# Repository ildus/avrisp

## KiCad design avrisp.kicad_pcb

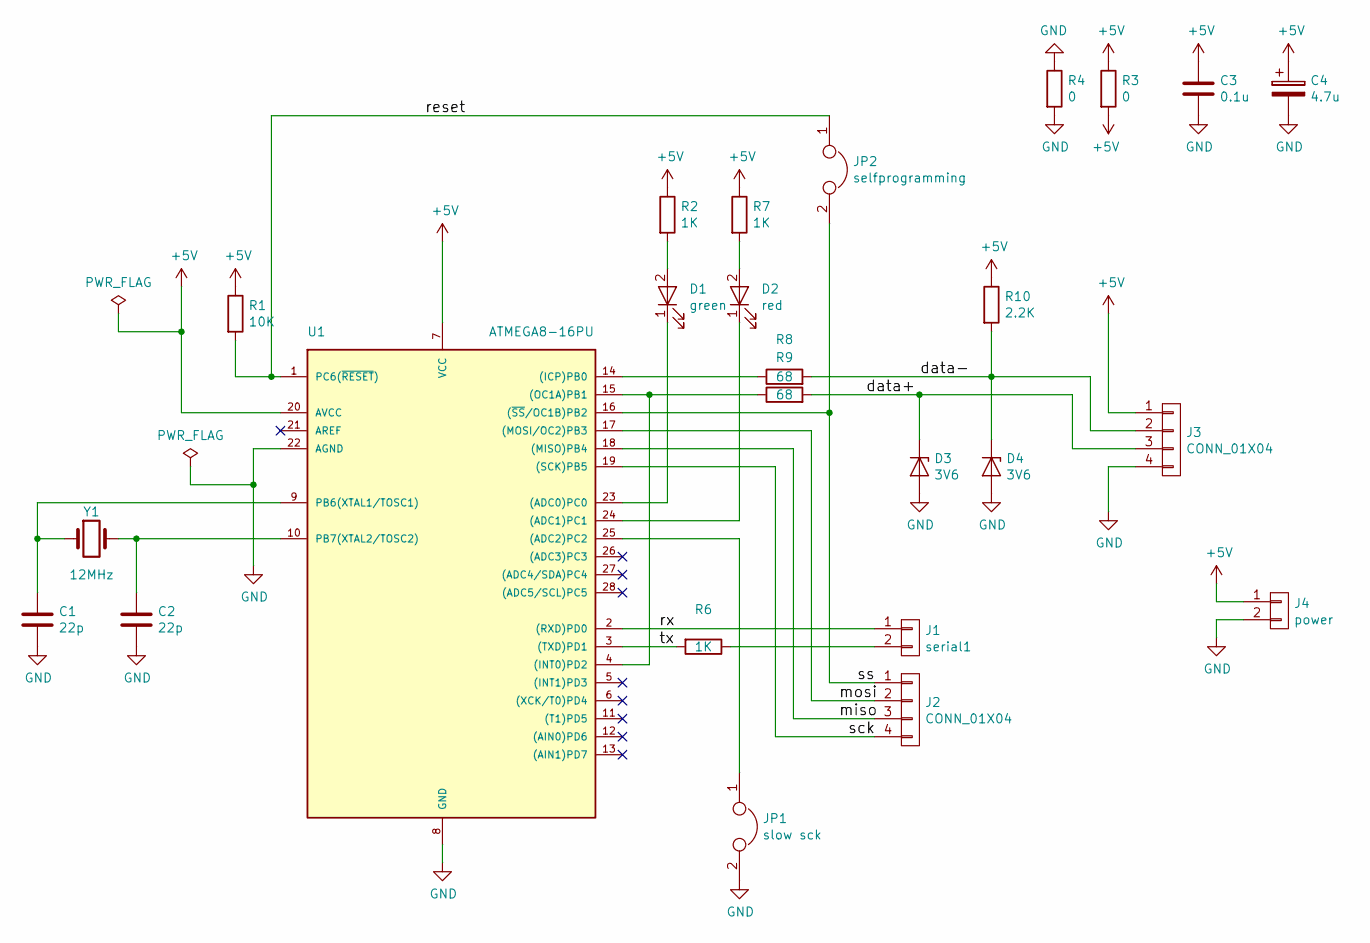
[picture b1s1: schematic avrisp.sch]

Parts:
C1, C2: 22p; C_0805_HandSoldering
C3: 0.1u; C_0805_HandSoldering
C4: 4.7u; CP_Radial_D4.0mm_P2.00mm
D1: green; LED_1206
D2: red; LED_1206
D3, D4: 3V6; SOT-23
J1: serial1; Molex_KK-6410-02_02x2.54mm_Straight
J2, J3: CONN_01X04; Molex_KK-6410-04_04x2.54mm_Straight
J4: power; Molex_KK-6410-02_02x2.54mm_Straight
JP1: slow sck; Molex_KK-6410-02_02x2.54mm_Straight
JP2: selfprogramming; Molex_KK-6410-02_02x2.54mm_Straight
R1: 10K; R_1206
R2, R6, R7: 1K; R_1206
R3, R4: 0; R_1206
R8, R9: 68; R_1206
R10: 2.2K; R_1206
U1: ATMEGA8-16PU; DIP-28_W7.62mm
Y1: 12MHz; Crystal_HC50_Vertical

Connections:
+5V: C3.1, C4.1, J3.1, J4.1, R1.1, R2.1, R3.1, R3.2, R7.1, R10.1, U1.7 (VCC), U1.20 (AVCC)
/data+: D3.3 (K), J3.3, R9.2
/data-: D4.3 (K), J3.2, R8.2, R10.2
/miso: J2.3, U1.18 ((MISO)PB4)
/mosi: J2.2, U1.17 ((MOSI/OC2)PB3)
/reset: JP2.1, R1.2, U1.1 (PC6(~RESET~))
/rx: J1.1, U1.2 ((RXD)PD0)
/sck: J2.4, U1.19 ((SCK)PB5)
/ss: J2.1, JP2.2, U1.16 ((~SS~/OC1B)PB2)
/tx: R6.2, U1.3 ((TXD)PD1)
GND: C1.2, C2.2, C3.2, C4.2, D3.1 (A), D4.1 (A), J3.4, J4.2, JP1.2, R4.1, R4.2, U1.8 (GND), U1.22 (AGND)
unnamed: C1.1, U1.9 (PB6(XTAL1/TOSC1)), Y1.1
unnamed: C2.1, U1.10 (PB7(XTAL2/TOSC2)), Y1.2
unnamed: D1.1 (K), U1.23 ((ADC0)PC0)
unnamed: D1.2 (A), R2.2
unnamed: D2.1 (K), U1.24 ((ADC1)PC1)
unnamed: D2.2 (A), R7.2
unnamed: J1.2, R6.1
unnamed: JP1.1, U1.25 ((ADC2)PC2)
unnamed: R8.1, U1.14 ((ICP)PB0)
unnamed: R9.1, U1.4 ((INT0)PD2), U1.15 ((OC1A)PB1)

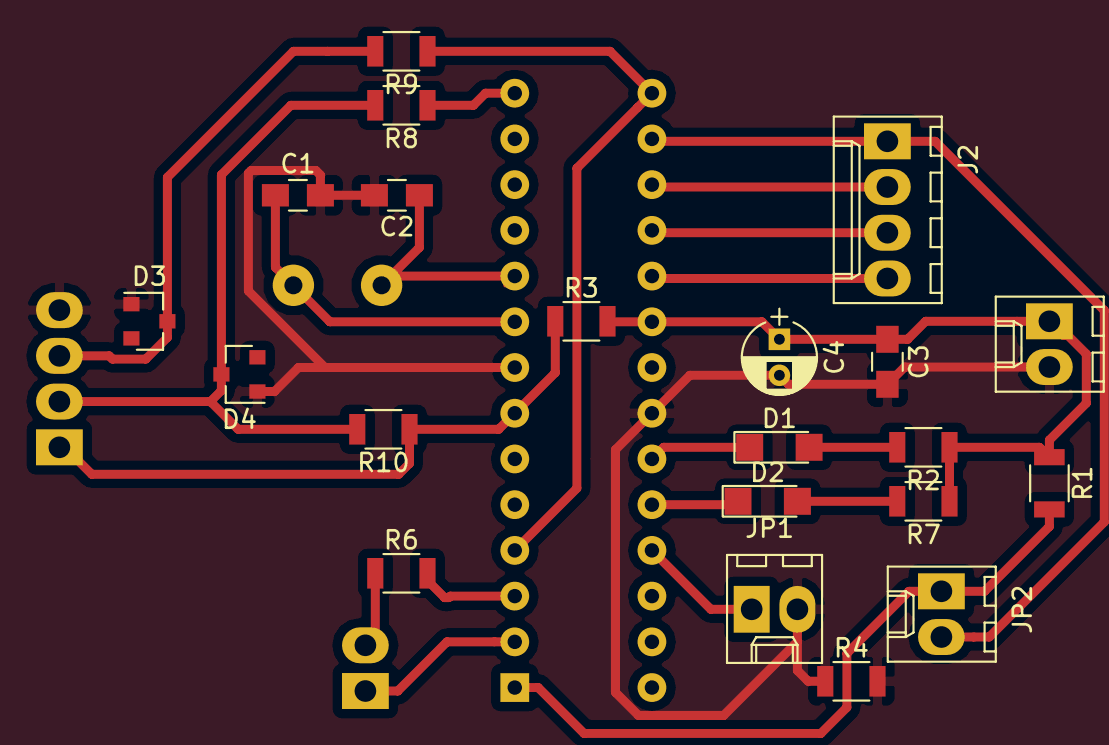
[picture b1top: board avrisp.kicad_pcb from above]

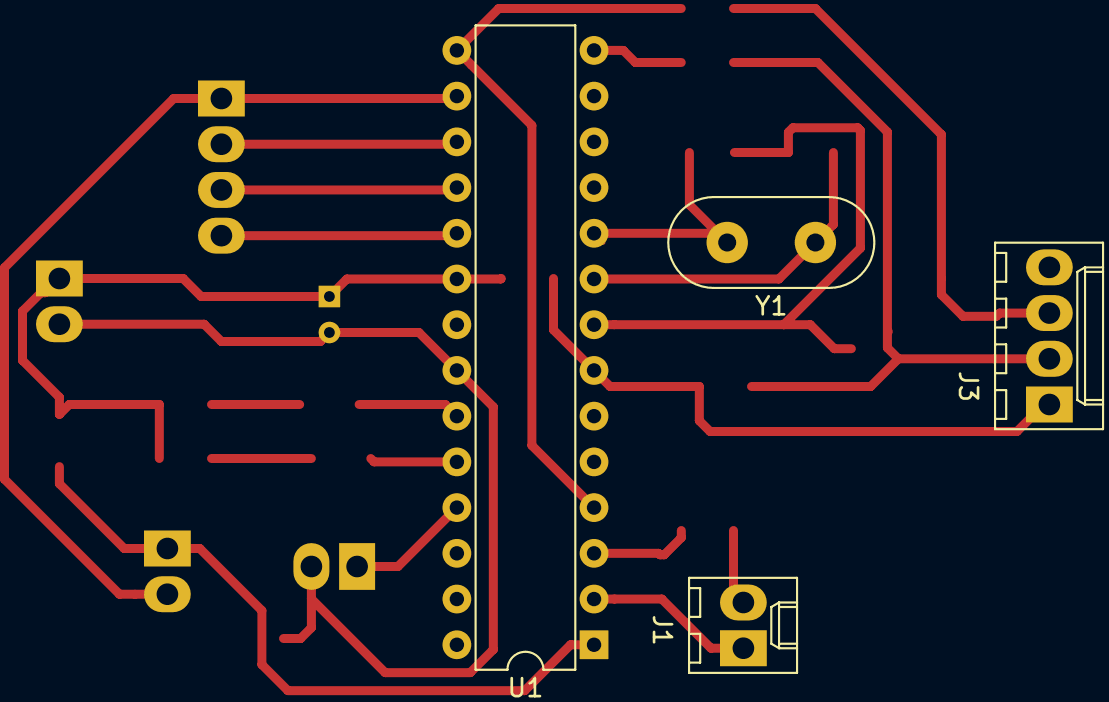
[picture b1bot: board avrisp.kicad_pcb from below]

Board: 2 copper layers, 25 parts (4 on the bottom side), 21 nets.

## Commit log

2017-05-21 initial
2017-05-21 Make few fixes
2017-05-21 Modify PCB
2017-05-22 Update PCB
2017-05-22 Finish PCB
2017-05-22 Make one side version
2017-05-22 Increase drill sizes
2017-05-25 last changes
2017-05-25 Add forgotten files
2017-05-26 Make one sided PCB but with smd components
